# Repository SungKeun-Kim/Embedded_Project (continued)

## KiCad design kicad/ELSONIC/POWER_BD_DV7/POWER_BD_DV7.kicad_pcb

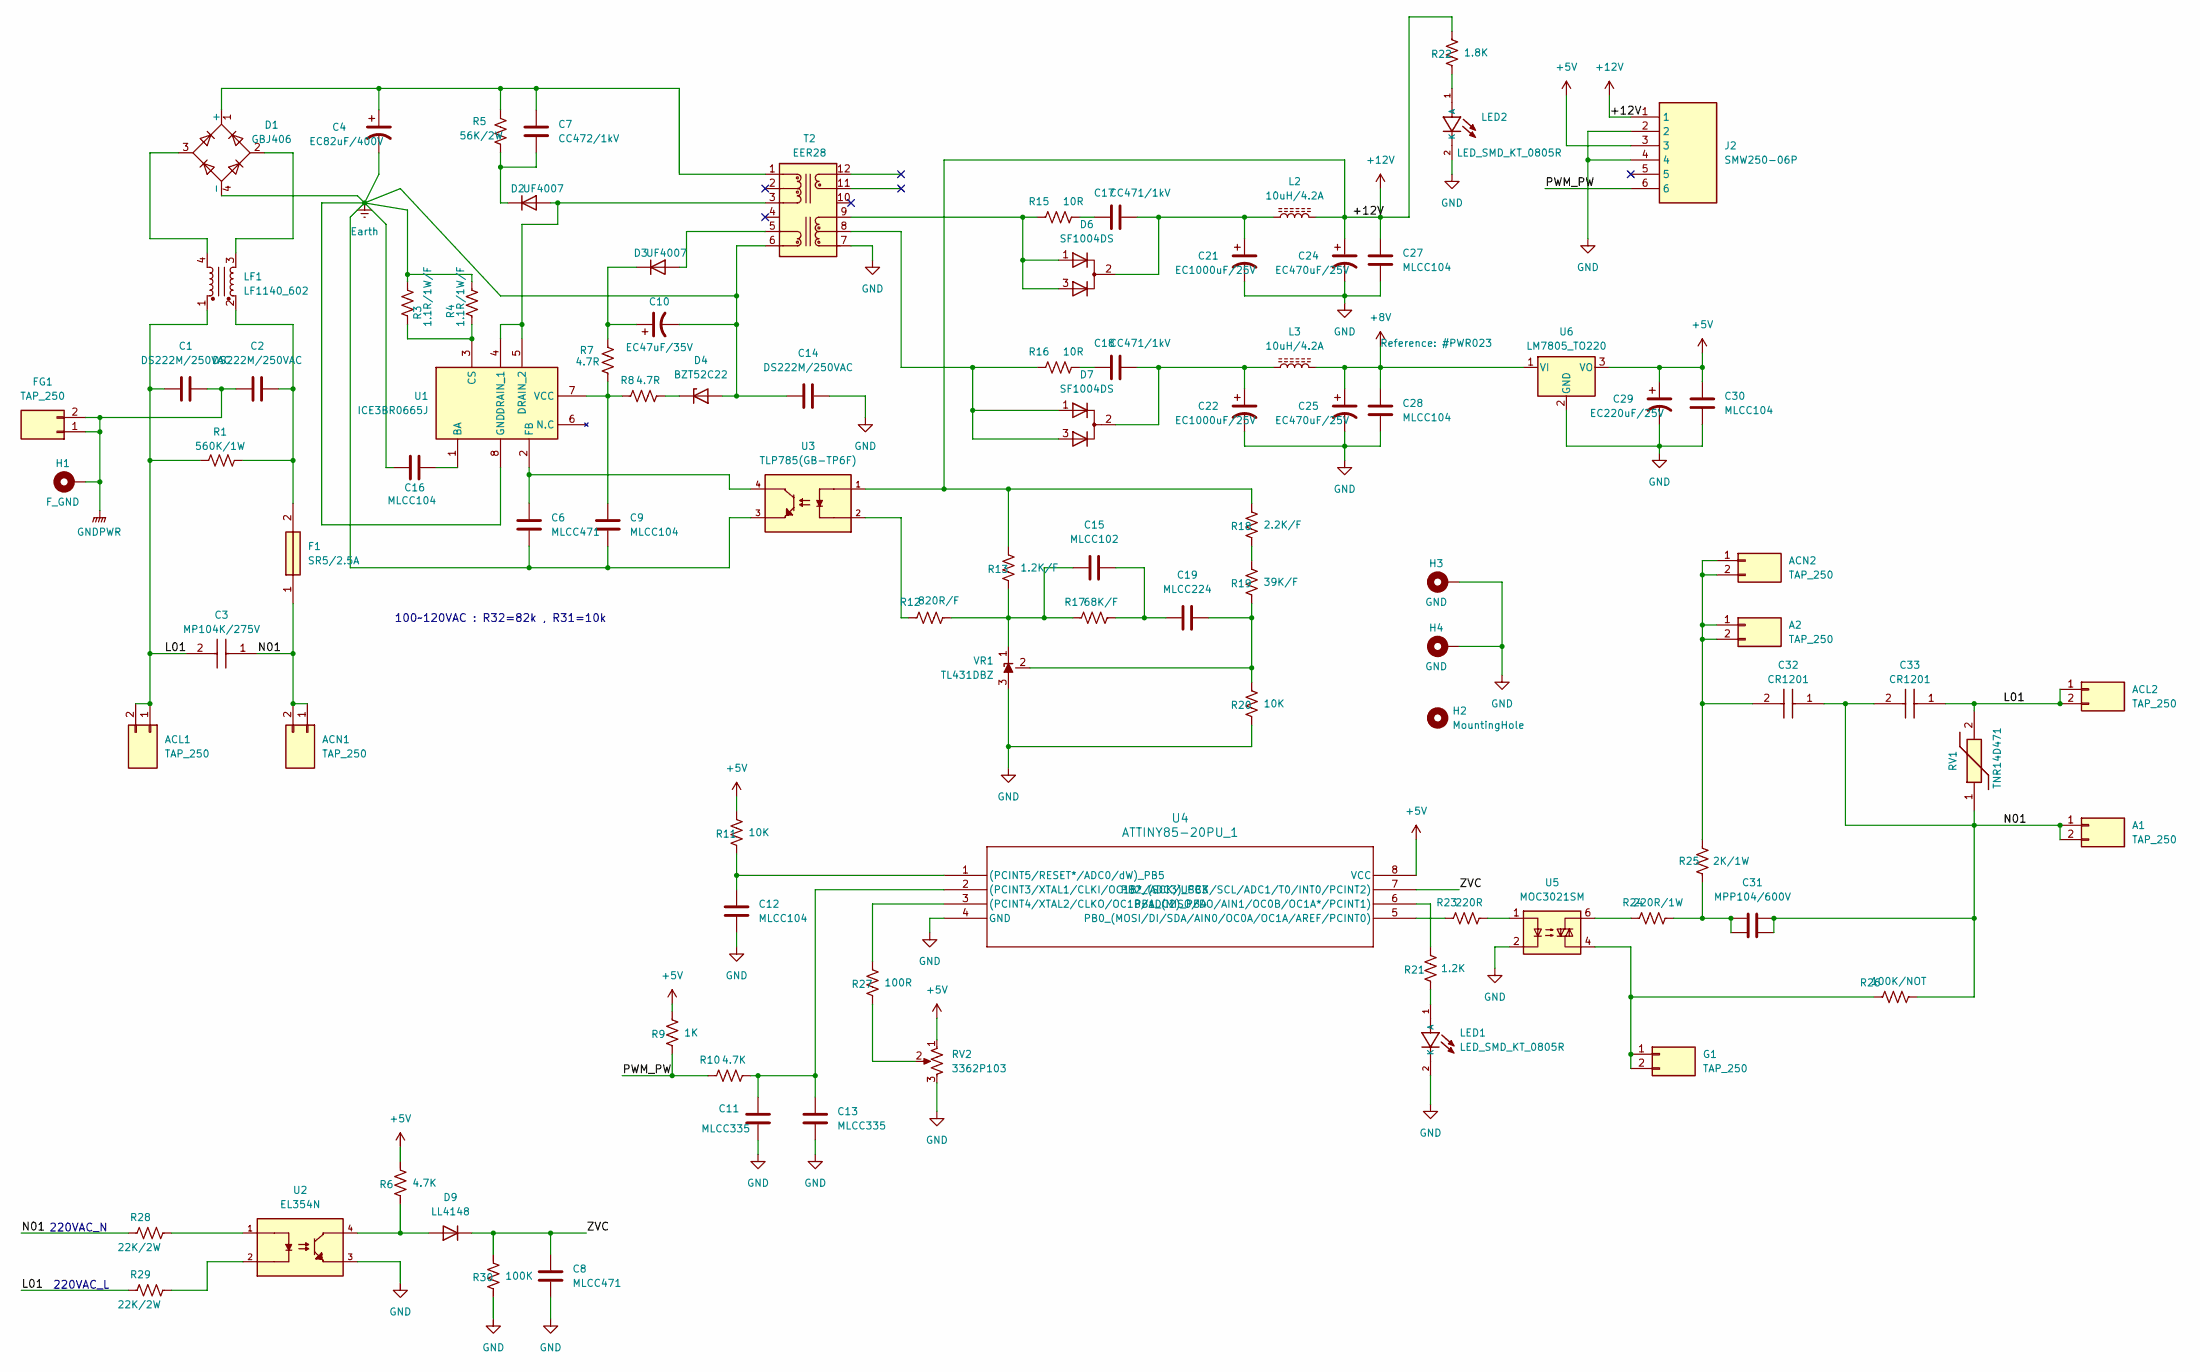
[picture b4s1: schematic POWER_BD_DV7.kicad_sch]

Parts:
A1, A2: TAP_250
ACL1, ACL2: TAP_250
ACN1, ACN2: TAP_250
C1, C2, C14: DS222M/250VAC; DS222M
C3: MP104K/275V; 104K_275V
C4: EC82uF/400V; 82uF_400V
C6, C8: MLCC471; C_3216Metric; LCSC C106069
C7: CC472/1kV; C_3216Metric; LCSC C9192
C9, C12, C16, C27, C28, C30: MLCC104; C_3216Metric; LCSC C24497
C10: EC47uF/35V; CP_Elec_6.3x5.4; LCSC C970678
C11, C13: MLCC335; C_3216Metric; LCSC C3908730
C15: MLCC102; C_3216Metric; LCSC C1941
C17, C18: CC471/1kV; C_3216Metric; LCSC C9189
C19: MLCC224; C_3216Metric; LCSC C1857
C21, C22: EC1000uF/25V; CP_Radial_D10.0mm_P5.00mm
C24, C25: EC470uF/25V; CP_Radial_D10.0mm_P5.00mm
C29: EC220uF/25V; CP_Elec_6.3x7.7; LCSC C2992606
C31: MPP104/600V; C_PP_P10.0mm_P21.2mm
C32, C33: CR1201; SPARK_KILLER
D1: GBJ406
D2, D3: UF4007; D_SMA; LCSC C81191
D4: BZT52C22; D_SOD-123; LCSC C2108
D6, D7: SF1004DS; TO-252-2; LCSC C3011035
D9: LL4148; LL4148_MELF; LCSC C68883
F1: SR5/2.5A; SR525ABK
FG1: TAP_250
G1: TAP_250
H1: F_GND; MTHole_3.5mm_7.5mmPad_GND
H2: MountingHole; MTHole_3.5mm
H3, H4: GND; MTHole_3.5mm_7.5mmPad_GND
J2: SMW250-06P; SMW250_06P
L2, L3: 10uH/4.2A; L_Sumida_CDMC6D28_7.25x6.5mm; LCSC C436542
LED1, LED2: LED_SMD_KT_0805R; LED_2012Metric; LCSC C2295
LF1: LF1140_602; LF1140
R1: 560K/1W; R_Axial_1W_P14.6mm
R3, R4: 1.1R/1W/F; R_6332Metric; LCSC C5154651
R5: 56K/2W; R_Axial_2W_P20.32mm
R6, R10: 4.7K; R_3216Metric; LCSC C17936
R7, R8: 4.7R; R_3216Metric; LCSC C2907501
R9: 1K; R_3216Metric; LCSC C4410
R11, R20: 10K; R_3216Metric; LCSC C17902
R12: 820R/F; R_3216Metric; LCSC C17984
R13: 1.2K/F; R_3216Metric; LCSC C17891
R15, R16: 10R; R_4532Metric; LCSC C2933875
R17: 68K/F; R_3216Metric; LCSC C137239
R18: 2.2K/F; R_3216Metric; LCSC C140044
R19: 39K/F; R_3216Metric; LCSC C18008
R21: 1.2K; R_3216Metric; LCSC C26035
R22: 1.8K; R_3216Metric; LCSC C102291
R23: 220R; R_3216Metric; LCSC C17957
R24: 220R/1W; R_6332Metric; LCSC C38808
R25: 2K/1W; R_6332Metric; LCSC C37457
R26: 100K/NOT; R_Axial_0.25W_P10.16mm
R27: 100R; R_3216Metric; LCSC C17901
R28, R29: 22K/2W; R_Axial_2W_P20.32mm
R30: 100K; R_3216Metric; LCSC C17900
RV1: TNR14D471; TNR14D_P7.62
RV2: 3362P103; TRIM_3362P
T2: EER28; EER28_35_12P
U1: ICE3BR0665J; DIP-8_W7.62mm_Socket
U2: EL354N; SOIC-4_EL354_P2.54mm; LCSC C188348
U3: TLP785(GB-TP6F); SOP-4_7.5x4.1mm_P2.54mm; LCSC C45445
U4: ATTINY85-20PU_1; DIP-8_W7.62mm_Socket
U5: MOC3021SM; SOIC-6_P2.54mm; LCSC C115465
U6: LM7805_TO220; TO-252-2; LCSC C21706
VR1: TL431DBZ; SOT-23-3; LCSC C23892

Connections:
+5V: C29.1, C30.2, J2.3, R6.2, R9.2, R11.2, RV2.1, U4.8 (VCC), U6.3 (VO)
+8V: C25.1, C28.2, L3.2, U6.1 (VI)
+12V: C24.1, C27.2, J2.1, L2.2, R13.2, R18.2, R22.2, U3.1
/L01: ACL1.1, ACL1.2, ACL2.1, ACL2.2, C1.1, C3.2, C33.1, LF1.1, R1.1, R29.1, RV1.2
/N01: A1.1, A1.2, ACN1.1, ACN1.2, C3.1, C31.2, C31.4, C32.1, C33.2, F1.1, R26.2, R28.1, RV1.1
/PWM_PW: J2.6, R9.1, R10.1
/ZVC: C8.2, D9.1 (K), R30.2, U4.7 (PB2_(SCK/USCK/SCL/ADC1/T0/INT0/PCINT2))
Earth: C4.2, C6.1, C9.1, C10.2, C14.1, C16.2, D1.4 (-), D4.2 (A), R3.1, R4.1, T2.6 (Vcc_GND), U1.8 (GND), U3.3
GND: C8.1, C11.1, C12.1, C13.1, C14.2, C21.2, C22.2, C24.2, C25.2, C27.1, C28.1, C29.2, C30.1, H3.1 (1_1), H4.1 (1_1), J2.2, J2.4, LED1.2 (K), LED2.2 (K), R20.1, R30.1, RV2.3, T2.7 (N_GND1), U2.3, U4.4 (GND), U5.2, U6.2 (GND), VR1.3 (A)
GNDPWR: C1.2, C2.1, FG1.1, FG1.2, H1.1 (1_1)
unnamed: A2.1, A2.2, ACN2.1, ACN2.2, C32.2, R25.1
unnamed: C2.2, F1.2, LF1.2, R1.2
unnamed: C15.2, C19.1, R17.2
unnamed: C17.1, R15.2
unnamed: C18.1, R16.2
unnamed: C31.1, C31.3, R24.2, R25.2
unnamed: C4.1, C7.1, D1.1 (+), R5.1, T2.1 (P0)
unnamed: D1.2, LF1.3
unnamed: D1.3, LF1.4
unnamed: D2.2 (A), T2.3 (P2), U1.4 (DRAIN_1), U1.5 (DRAIN_2)
unnamed: C7.2, D2.1 (K), R5.2
unnamed: D3.2 (A), T2.5 (Vcc)
unnamed: C10.1, D3.1 (K), R7.1
unnamed: D4.1 (K), R8.2
unnamed: C17.2, C21.1, D6.2 (K), L2.1
unnamed: C18.2, C22.1, D7.2 (K), L3.1
unnamed: D9.2 (A), R6.1, U2.4
unnamed: G1.1, G1.2, R26.1, U5.4
unnamed: LED1.1 (A), R21.2
unnamed: LED2.1 (A), R22.1
unnamed: R12.1, U3.2
unnamed: R18.1, R19.2
unnamed: R23.2, U5.1
unnamed: R24.1, U5.6
unnamed: R27.1, RV2.2
unnamed: R28.2, U2.1
unnamed: R29.2, U2.2
unnamed: D7.1 (A), D7.3 (A), R16.1, T2.8 (N1)
unnamed: D6.1 (A), D6.3 (A), R15.1, T2.9 (N2)
unnamed: C16.1, U1.1 (BA)
unnamed: R3.2, R4.2, U1.3 (CS)
unnamed: C6.2, U1.2 (FB), U3.4
unnamed: C9.2, R7.2, R8.1, U1.7 (VCC)
unnamed: C11.2, C13.2, R10.2, U4.2 ((PCINT3/XTAL1/CLKI/OC1B*/ADC3)_PB3)
unnamed: R27.2, U4.3 ((PCINT4/XTAL2/CLKO/OC1B/ADC2)_PB4)
unnamed: C12.2, R11.1, U4.1 ((PCINT5/RESET*/ADC0/dW)_PB5)
unnamed: R23.1, U4.5 (PB0_(MOSI/DI/SDA/AIN0/OC0A/OC1A/AREF/PC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)
unnamed: R21.1, U4.6 (PB1_(MISO/DO/AIN1/OC0B/OC1A*/PCINT1))
unnamed: C15.1, R12.2, R13.1, R17.1, VR1.1 (K)
unnamed: C19.2, R19.1, R20.2, VR1.2 (REF)

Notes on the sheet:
220VAC_N
100~120VAC : R32=82k , R31=10k
220VAC_L

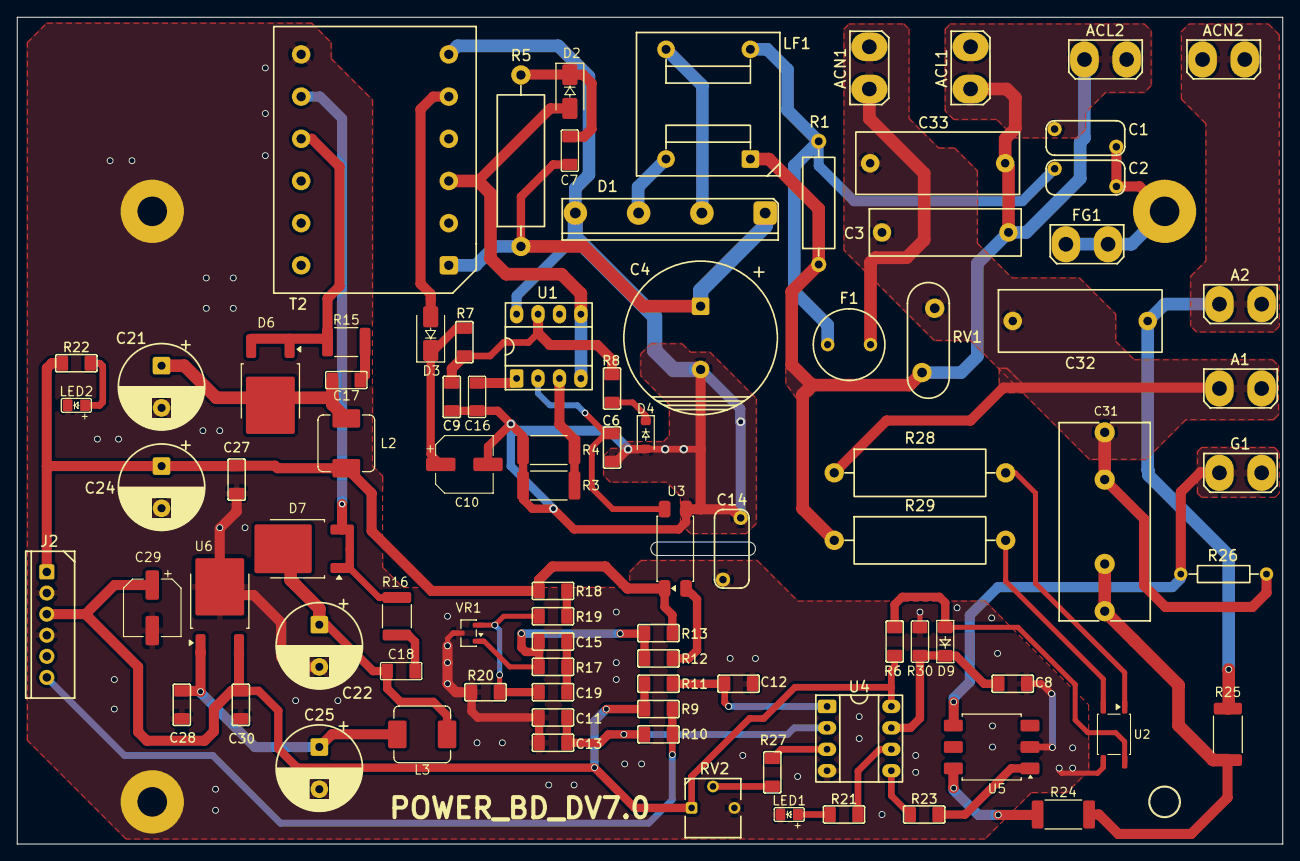
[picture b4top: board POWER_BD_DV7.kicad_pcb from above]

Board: 2 copper layers, 150.0 x 98.0 mm, 93 parts (0 on the bottom side), 50 nets.

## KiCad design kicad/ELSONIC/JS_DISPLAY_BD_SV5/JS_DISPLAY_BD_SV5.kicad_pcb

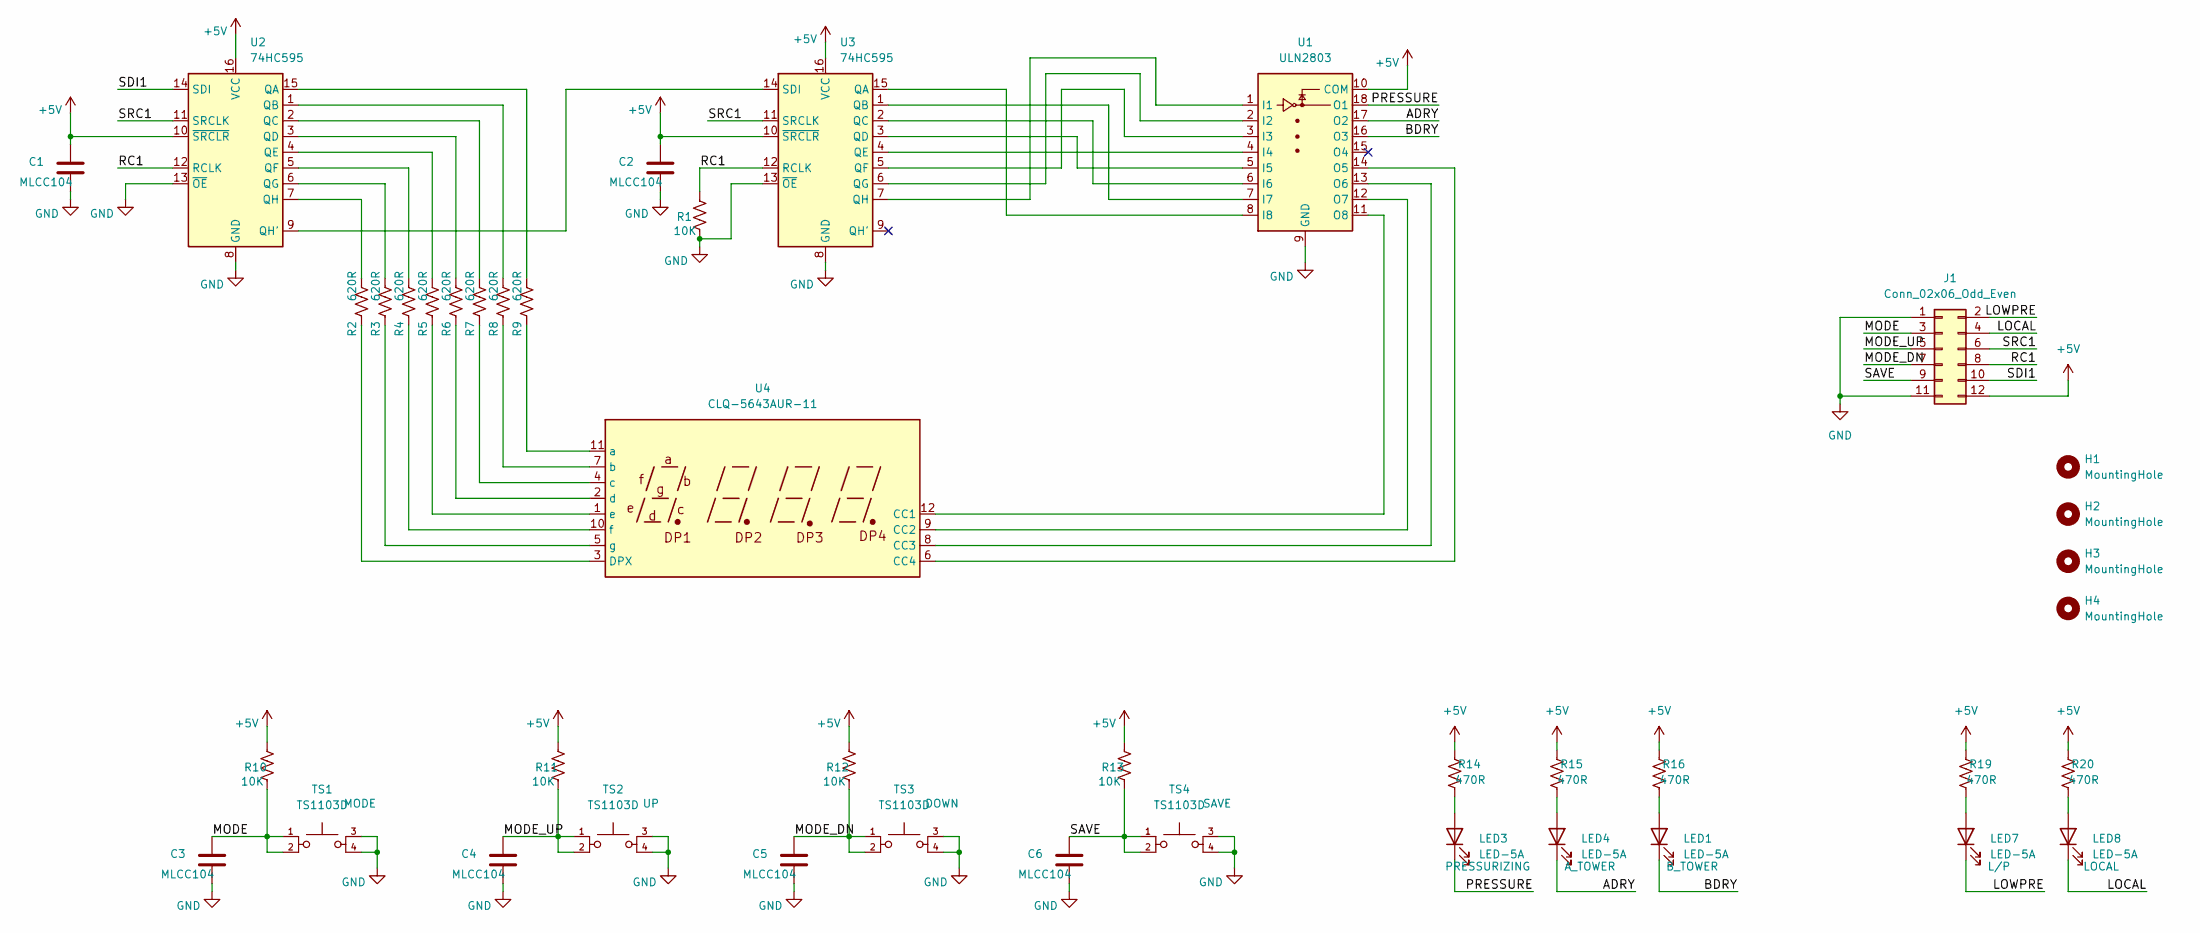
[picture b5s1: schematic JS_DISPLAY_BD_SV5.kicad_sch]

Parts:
C1, C2, C3, C4, C5, C6: MLCC104; C_3216Metric; LCSC C1945
H1, H2, H3, H4: MountingHole; MTHole_3.5mm_ANTICOPPER
J1: Conn_02x06_Odd_Even; IDC-Header_2x06_P2.54mm_Vertical
LED1, LED3, LED4, LED7, LED8: LED-5A; LED_D5.0mm
R1, R10, R11, R12, R13: 10K; R_3216Metric; LCSC C136460
R2, R3, R4, R5, R6, R7, R8, R9: 620R; R_3216Metric; LCSC C966344
R14, R15, R16, R19, R20: 470R; R_3216Metric; LCSC C114948
TS1, TS2, TS3, TS4: TS1103D; SW_PUSH-12mm
U1: ULN2803; SOP-18_7.495x11.515mm_P1.27mm; LCSC C18164409
U2, U3: 74HC595; SOIC-16_3.9x9.9mm_P1.27mm; LCSC C5947
U4: CLQ-5643AUR-11

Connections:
+5V: C1.2, C2.2, J1.12, R10.2, R11.2, R12.2, R13.2, R14.2, R15.2, R16.2, R19.2, R20.2, U1.10 (COM), U2.10 (~SRCLR), U2.16 (VCC), U3.10 (~SRCLR), U3.16 (VCC)
/ADRY: LED4.1 (K), U1.17 (O2)
/BDRY: LED1.1 (K), U1.16 (O3)
/LOCAL: J1.4, LED8.1 (K)
/LOWPRE: J1.2, LED7.1 (K)
/MODE: C3.2, J1.3, R10.1, TS1.1, TS1.2
/MODE_DN: C5.2, J1.7, R12.1, TS3.1, TS3.2
/MODE_UP: C4.2, J1.5, R11.1, TS2.1, TS2.2
/PRESSURE: LED3.1 (K), U1.18 (O1)
/RC1: J1.8, R1.2, U2.12 (RCLK), U3.12 (RCLK)
/SAVE: C6.2, J1.9, R13.1, TS4.1, TS4.2
/SDI1: J1.10, U2.14 (SDI)
/SRC1: J1.6, U2.11 (SRCLK), U3.11 (SRCLK)
GND: C1.1, C2.1, C3.1, C4.1, C5.1, C6.1, J1.1, J1.11, R1.1, TS1.3, TS1.4, TS2.3, TS2.4, TS3.3, TS3.4, TS4.3, TS4.4, U1.9 (GND), U2.8 (GND), U2.13 (~OE), U3.8 (GND), U3.13 (~OE)
unnamed: LED1.2 (A), R16.1
unnamed: LED3.2 (A), R14.1
unnamed: LED4.2 (A), R15.1
unnamed: LED7.2 (A), R19.1
unnamed: LED8.2 (A), R20.1
unnamed: U1.1 (I1), U3.7 (QH)
unnamed: U1.2 (I2), U3.6 (QG)
unnamed: U1.3 (I3), U3.5 (QF)
unnamed: U1.4 (I4), U3.4 (QE)
unnamed: U1.5 (I5), U3.3 (QD)
unnamed: U1.6 (I6), U3.2 (QC)
unnamed: U1.7 (I7), U3.1 (QB)
unnamed: U1.8 (I8), U3.15 (QA)
unnamed: U1.14 (O5), U4.6 (CC4)
unnamed: U1.13 (O6), U4.8 (CC3)
unnamed: U1.12 (O7), U4.9 (CC2)
unnamed: U1.11 (O8), U4.12 (CC1)
unnamed: R9.2, U2.15 (QA)
unnamed: R8.2, U2.1 (QB)
unnamed: R7.2, U2.2 (QC)
unnamed: R6.2, U2.3 (QD)
unnamed: R5.2, U2.4 (QE)
unnamed: R4.2, U2.5 (QF)
unnamed: R3.2, U2.6 (QG)
unnamed: U2.9 (QH'), U3.14 (SDI)
unnamed: R2.2, U2.7 (QH)
unnamed: R2.1, U4.3 (DPX)
unnamed: R9.1, U4.11 (a)
unnamed: R8.1, U4.7 (b)
unnamed: R7.1, U4.4 (c)
unnamed: R6.1, U4.2 (d)
unnamed: R5.1, U4.1 (e)
unnamed: R4.1, U4.10 (f)
unnamed: R3.1, U4.5 (g)

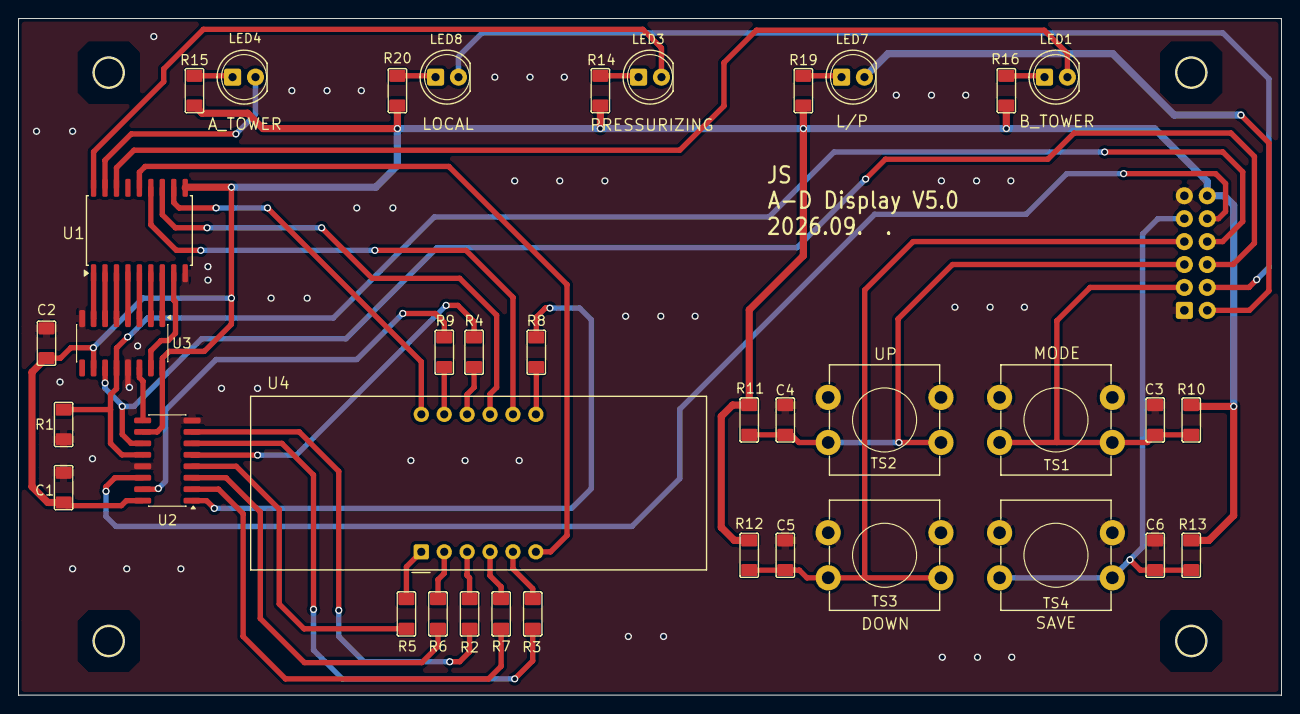
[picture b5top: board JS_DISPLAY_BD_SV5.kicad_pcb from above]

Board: 2 copper layers, 140.0 x 75.0 mm, 42 parts (1 on the bottom side), 48 nets.

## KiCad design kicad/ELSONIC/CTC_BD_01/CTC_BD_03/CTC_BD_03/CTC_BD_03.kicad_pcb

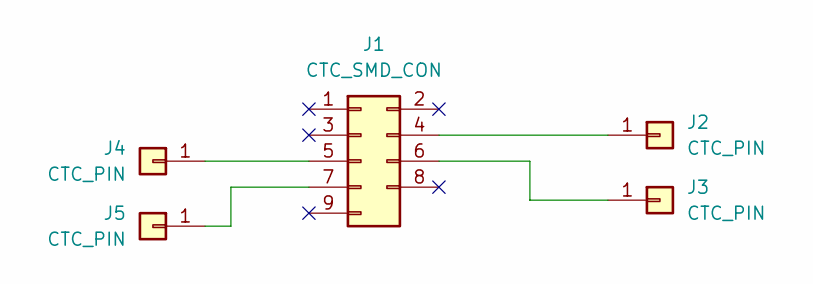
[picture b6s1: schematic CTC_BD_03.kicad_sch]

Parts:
J1: CTC_SMD_CON
J2, J3, J4, J5: CTC_PIN

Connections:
unnamed: J1.4, J2.1 (Pin_1_1)
unnamed: J1.5, J4.1 (Pin_1_1)
unnamed: J1.6, J3.1 (Pin_1_1)
unnamed: J1.7, J5.1 (Pin_1_1)

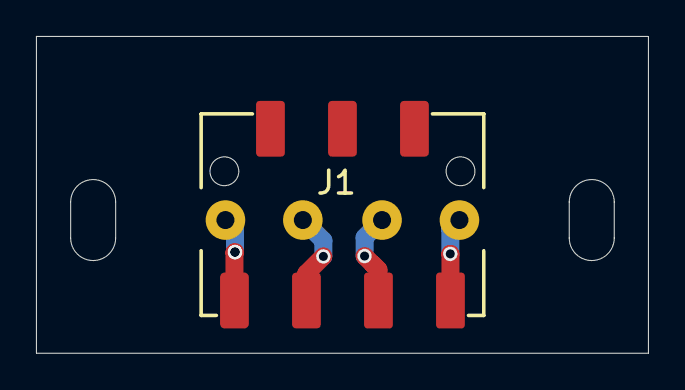
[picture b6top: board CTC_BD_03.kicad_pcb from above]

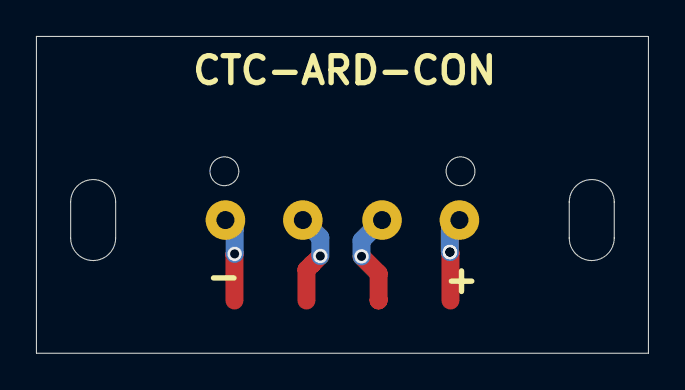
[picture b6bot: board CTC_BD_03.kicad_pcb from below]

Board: 2 copper layers, 34.0 x 17.6 mm, 5 parts (4 on the bottom side), 4 nets.

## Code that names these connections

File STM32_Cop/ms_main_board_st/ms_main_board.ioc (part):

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Mcu.Name=STM32G474R(B-C-E)Tx
Mcu.Package=LQFP64
Mcu.UserName=STM32G474RBTx
PA0.GPIOParameters=GPIO_Label
PA0.GPIO_Label=ADC1_IN1
PA0.Signal=ADC1_IN1
PA1.GPIOParameters=GPIO_Label
PA1.GPIO_Label=ADC1_IN2
PA1.Signal=ADC1_IN2
PA10.GPIOParameters=GPIO_Label
PA10.GPIO_Label=LOW_ALARM
PA10.Signal=GPIO_Output
PA11.GPIOParameters=GPIO_Label
PA11.GPIO_Label=GOING
PA11.Signal=GPIO_Output
PA12.GPIOParameters=GPIO_Label
PA12.GPIO_Label=TOTAL_ALARM
PA12.Signal=GPIO_Output
PA13.GPIOParameters=GPIO_Label
PA13.GPIO_Label=SWDIO
PA13.Mode=Serial_Wire
PA13.Signal=SYS_JTMS-SWDIO
PA14.GPIOParameters=GPIO_Label
PA14.GPIO_Label=SWCLK
PA14.Mode=Serial_Wire
PA14.Signal=SYS_JTCK-SWCLK
PA15.GPIOParameters=GPIO_PuPd,GPIO_Label
PA15.GPIO_Label=REMOTE_M
PA15.GPIO_PuPd=GPIO_PULLUP
PA15.Signal=GPIO_Input
PA2.GPIOParameters=GPIO_Speed,GPIO_Label
PA2.GPIO_Label=USART2_TX
PA2.GPIO_Speed=GPIO_SPEED_FREQ_HIGH
PA2.Signal=USART2_TX
PA3.GPIOParameters=GPIO_Speed,GPIO_PuPd,GPIO_Label
PA3.GPIO_Label=USART2_RX
PA3.GPIO_PuPd=GPIO_PULLUP
PA3.GPIO_Speed=GPIO_SPEED_FREQ_HIGH
PA3.Signal=USART2_RX
PA4.GPIOParameters=GPIO_Label
PA4.GPIO_Label=DAC1_OUT1
PA4.Signal=COMP_DAC11_group
PA6.GPIOParameters=GPIO_Label
PA6.GPIO_Label=ADC2_IN3
PA6.Signal=ADC2_IN3
PA7.GPIOParameters=GPIO_Label
PA7.GPIO_Label=ADC2_IN4
PA7.Signal=ADC2_IN4
PA8.GPIOParameters=GPIO_Speed,GPIO_Label
PA8.GPIO_Label=CHA1
PA8.GPIO_Speed=GPIO_SPEED_FREQ_VERY_HIGH
PA8.Signal=HRTIM1_CHA1
PA9.GPIOParameters=GPIO_Speed,GPIO_Label
PA9.GPIO_Label=CHA2
PA9.GPIO_Speed=GPIO_SPEED_FREQ_VERY_HIGH
PA9.Signal=HRTIM1_CHA2
PB0.GPIOParameters=GPIO_Speed,GPIO_Label
PB0.GPIO_Label=DE_RS485
PB0.GPIO_Speed=GPIO_SPEED_FREQ_HIGH
PB0.Signal=GPIO_Output
PB1.GPIOParameters=GPIO_Speed,GPIO_Label
PB1.GPIO_Label=RE_RS485_N
PB1.GPIO_Speed=GPIO_SPEED_FREQ_HIGH
PB1.Signal=GPIO_Output
PB10.GPIOParameters=GPIO_Speed,GPIO_Label
PB10.GPIO_Label=D0
PB10.GPIO_Speed=GPIO_SPEED_FREQ_MEDIUM
PB10.Signal=GPIO_Output
PB11.GPIOParameters=GPIO_Speed,GPIO_Label
PB11.GPIO_Label=D1
PB11.GPIO_Speed=GPIO_SPEED_FREQ_MEDIUM
PB11.Signal=GPIO_Output
PB12.GPIOParameters=GPIO_Speed,GPIO_Label
PB12.GPIO_Label=D2
PB12.GPIO_Speed=GPIO_SPEED_FREQ_MEDIUM
PB12.Signal=GPIO_Output
PB13.GPIOParameters=GPIO_Speed,GPIO_Label
PB13.GPIO_Label=D3
PB13.GPIO_Speed=GPIO_SPEED_FREQ_MEDIUM
PB13.Signal=GPIO_Output
PB14.GPIOParameters=GPIO_Speed,GPIO_Label
PB14.GPIO_Label=D4
PB14.GPIO_Speed=GPIO_SPEED_FREQ_MEDIUM
PB14.Signal=GPIO_Output
PB15.GPIOParameters=GPIO_Speed,GPIO_Label
PB15.GPIO_Label=D5
PB15.GPIO_Speed=GPIO_SPEED_FREQ_MEDIUM
PB15.Signal=GPIO_Output
PB3.GPIOParameters=GPIO_Label
PB3.GPIO_Label=HIGH_ALARM
PB3.Signal=GPIO_Output
PB4.GPIOParameters=GPIO_Label
PB4.GPIO_Label=TD_ALARM
PB4.Signal=GPIO_Output
PB6.GPIOParameters=GPIO_Speed,GPIO_Label
PB6.GPIO_Label=USART1_TX
PB6.GPIO_Speed=GPIO_SPEED_FREQ_HIGH
PB6.Signal=USART1_TX
PB7.GPIOParameters=GPIO_Speed,GPIO_Label
PB7.GPIO_Label=USART1_RX
PB7.GPIO_Speed=GPIO_SPEED_FREQ_HIGH
PB7.Signal=USART1_RX
PB8-BOOT0.GPIOParameters=GPIO_PuPd,GPIO_Label
PB8-BOOT0.GPIO_Label=BOOT0
PB8-BOOT0.GPIO_PuPd=GPIO_NOPULL
PB8-BOOT0.Signal=GPIO_Input
PC0.GPIOParameters=GPIO_PuPd,GPIO_Label
PC0.GPIO_Label=START_STOP
PC0.GPIO_PuPd=GPIO_PULLUP
PC0.Signal=GPIO_Input
PC1.GPIOParameters=GPIO_PuPd,GPIO_Label
PC1.GPIO_Label=MODE
PC1.GPIO_PuPd=GPIO_PULLUP
PC1.Signal=GPIO_Input
PC10.GPIOParameters=GPIO_PuPd,GPIO_Label
PC10.GPIO_Label=BCD_BIT1
PC10.GPIO_PuPd=GPIO_PULLUP
PC10.Signal=GPIO_Input
PC11.GPIOParameters=GPIO_PuPd,GPIO_Label
PC11.GPIO_Label=BCD_BIT2
PC11.GPIO_PuPd=GPIO_PULLUP
PC11.Signal=GPIO_Input
PC12.GPIOParameters=GPIO_PuPd,GPIO_Label
PC12.GPIO_Label=BCD_BIT3
PC12.GPIO_PuPd=GPIO_PULLUP
PC12.Signal=GPIO_Input
PC14-OSC32_IN.GPIOParameters=GPIO_Speed,GPIO_Label
PC14-OSC32_IN.GPIO_Label=CLK_LCD
PC14-OSC32_IN.GPIO_Speed=GPIO_SPEED_FREQ_MEDIUM
PC14-OSC32_IN.Signal=GPIO_Output
PC15-OSC32_OUT.GPIOParameters=GPIO_Speed,GPIO_Label
PC15-OSC32_OUT.GPIO_Label=CLK_LED
PC15-OSC32_OUT.GPIO_Speed=GPIO_SPEED_FREQ_MEDIUM
PC15-OSC32_OUT.Signal=GPIO_Output
PC2.GPIOParameters=GPIO_PuPd,GPIO_Label
PC2.GPIO_Label=UP
PC2.GPIO_PuPd=GPIO_PULLUP
PC2.Signal=GPIO_Input
PC3.GPIOParameters=GPIO_PuPd,GPIO_Label
PC3.GPIO_Label=DOWN
PC3.GPIO_PuPd=GPIO_PULLUP
PC3.Signal=GPIO_Input
PC4.GPIOParameters=GPIO_PuPd,GPIO_Label
PC4.GPIO_Label=SET
PC4.GPIO_PuPd=GPIO_PULLUP
PC4.Signal=GPIO_Input
PC5.GPIOParameters=GPIO_Label
PC5.GPIO_Label=BZ_OUT
PC5.Signal=GPIO_Output
PC6.GPIOParameters=GPIO_Label
PC6.GPIO_Label=LC_REL1
PC6.Signal=GPIO_Output
PC7.GPIOParameters=GPIO_Label
PC7.GPIO_Label=LC_REL2
PC7.Signal=GPIO_Output
PC8.GPIOParameters=GPIO_Label
PC8.GPIO_Label=LC_REL3
PC8.Signal=GPIO_Output
PC9.GPIOParameters=GPIO_Label
PC9.GPIO_Label=LC_REL4
PC9.Signal=GPIO_Output
PD2.GPIOParameters=GPIO_PuPd,GPIO_Label
PD2.GPIO_Label=SENSOR
PD2.GPIO_PuPd=GPIO_PULLUP
PD2.Signal=GPIO_Input
PF0-OSC_IN.Signal=RCC_OSC_IN
PF1-OSC_OUT.Signal=RCC_OSC_OUT
RCC.HSEState=RCC_HSE_ON
RCC.HSE_VALUE=8000000
RCC.SYSCLKFreq_VALUE=170000000
RCC.SYSCLKSource=RCC_SYSCLKSOURCE_PLLCLK
RCC.SYSCLKSourceVirtual=RCC_SYSCLKSOURCE_PLLCLK
board=custom

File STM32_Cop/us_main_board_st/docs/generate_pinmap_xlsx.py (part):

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
    groups = [
        ("🔊 초음파 발진 (TIM1 고급 타이머)", FILL_PWM, [
            ["PA8",  35, "TIM1_CH1 (AF6)",  "초음파 PWM 출력 — 하이사이드 게이트 드라이버(HIN) 입력", "Output", "Very High"],
            ["PB13", 28, "TIM1_CH1N (AF6)", "초음파 PWM 상보 출력 — 로우사이드 게이트 드라이버(LIN) 입력", "Output", "Very High"],
        ]),
        ("⚡ 위상제어 조광기 출력 (TIM3 → ATtiny85)", FILL_PWM, [
            ["PB0", 22, "TIM3_CH3 (AF2)", "ATtiny85 위상제어 듀티 지령 전달용 3kHz PWM 출력", "Output", "Medium"],
        ]),
        ("📡 내장 아날로그 — 비교기(COMP) + DAC3 + TIM2 캡처", FILL_INTERNAL, [
            ["PA1",  13, "COMP1_INP",              "전압(V) 위상 제로크로싱 검출 — 비교기 양(+)입력 【전용, ADC 비공유】", "Analog", "—"],
            ["PA7",  19, "COMP2_INP",              "전류(I) 위상 제로크로싱 검출 — 비교기 양(+)입력 (CT센서) 【전용, GPIO 비공유】", "Analog", "—"],
            ["—",    "—", "DAC3_CH1 → COMP1_INM",  "COMP1 반전입력 기준전압 (~1.65V = VDDA/2) 【내부 크로스바, 외부핀 없음】", "Internal", "—"],
            ["—",    "—", "DAC3_CH2 → COMP2_INM",  "COMP2 반전입력 기준전압 (~1.65V = VDDA/2) 【내부 크로스바, 외부핀 없음】", "Internal", "—"],
            ["—",    "—", "COMP1_OUT → TIM2_IC1",  "전압 제로크로싱 타임스탬프 캡처 【내부 라우팅】", "Internal", "—"],
            ["—",    "—", "COMP2_OUT → TIM2_IC2",  "전류 제로크로싱 타임스탬프 캡처 【내부 라우팅】", "Internal", "—"],
        ]),
        ("🎛️ ADC 입력 (가변저항 + 전류 센서)", FILL_ANALOG, [
            ["PA0",  12, "ADC1_IN1",  "보드 내장 가변저항 전압 (초음파 출력/위상 레벨)", "Analog", "—"],
            ["PB11", 26, "ADC1_IN14", "외부 판넬 가변저항 전압 (외부 출력/위상 레벨 지정)", "Analog", "—"],
            ["PA4",  16, "ADC2_IN17", "AC 전원 입력단 시스템 소모 전류 측정용 (ACS722/TMCS1100)", "Analog", "—"],
        ]),
        ("📺 LCD1602 (4비트 병렬 모드)", FILL_LCD, [
            ["PB12", 27, "GPIO_Output", "LCD RS (Register Select)", "Output", "Low"],
            ["PB14", 29, "GPIO_Output", "LCD EN (Enable)", "Output", "Low"],
            ["PB15", 30, "GPIO_Output", "LCD D4", "Output", "Low"],
            ["PC6",  31, "GPIO_Output", "LCD D5", "Output", "Low"],
            ["PC7",  32, "GPIO_Output", "LCD D6", "Output", "Low"],
            ["PC8",  33, "GPIO_Output", "LCD D7", "Output", "Low"],
        ]),
        ("🔘 택트 스위치 (내부 풀업, Active LOW)", FILL_BTN, [
            ["PC0", 8,  "GPIO_Input (PU)", "BTN_MENU — 메뉴 진입 및 상위 메뉴 복귀", "Input", "—"],
            ["PC1", 9,  "GPIO_Input (PU)", "BTN_UP — 메뉴 위로 / 값 증가", "Input", "—"],
            ["PC2", 10, "GPIO_Input (PU)", "BTN_DOWN — 메뉴 아래로 / 값 감소", "Input", "—"],
            ["PC3", 11, "GPIO_Input (PU)", "BTN_OK — 선택/확인 및 초음파 Start/Stop 겸용", "Input", "—"],
        ]),
        ("🔌 Modbus RS485 (USART2 + 방향 제어)", FILL_COMM, [
            ["PA2",  14, "USART2_TX (AF7)",    "RS485 TXD", "AF Output", "Very High"],
            ["PA3",  15, "USART2_RX (AF7)",    "RS485 RXD", "AF Input", "—"],
            ["PA5",  17, "GPIO_Output",         "RS485 DE (Driver Enable, HIGH=송신) — USART2 인접 배치", "Output", "High"],
            ["PA6",  18, "GPIO_Output",         "RS485 /RE (Receiver Enable, LOW=수신) — USART2 인접 배치", "Output", "High"],
            ["PC11", 46, "GPIO_Output",         "RS485 RTERM (종단 저항 120Ω ON/OFF 제어)", "Output", "Low"],
            ["PC12", 47, "GPIO_Input",          "Board_Detect (RS485 옵션 보드 장착 인식, 메뉴 연동)", "Input", "—"],
        ]),
        ("🔧 외부 제어 인터페이스 (스위치 입력 + 릴레이/부저 출력)", FILL_EXT, [
            ["PC4",  20, "GPIO_Output", "부저 출력 — 버튼 클릭음 + 에러 알람 겸용", "Output", "Low"],
            ["PC5",  21, "GPIO_Output", "End Signal 릴레이 — 사이클 종료 후 0.5초 ON", "Output", "Low"],
            ["PA12", 39, "GPIO_Output", "Fault 릴레이 — 에러 발생 상태 지시", "Output", "Low"],
            ["PA15", 44, "GPIO_Output", "Running 릴레이 — 정상 동작 상태 지시 (G4는 SWD 기본, 바로 사용)", "Output", "Low"],
            ["PB1",  23, "GPIO_Input",  "Remote ON/OFF — 외부 기기 리모트 제어 입력", "Input", "—"],
            ["PB2",  24, "GPIO_Input",  "Sweep 스위치 — 수동 스윕 분산 기능 푸쉬락", "Input", "—"],
            ["PB10", 25, "GPIO_Input",  "Timer 스위치 — 내장 타이머 사용 유무 푸쉬락", "Input", "—"],
        ]),
        ("🐛 디버그 / 시스템", FILL_DBG, [
            ["PA9",  36, "USART1_TX (AF7)", "디버그 메시지용 UART TX (115200bps, 선택사항)", "AF Output", "High"],
            ["PA10", 37, "USART1_RX (AF7)", "디버그 메시지 수신용 UART RX (선택사항)", "AF Input", "—"],
            ["PA13", 40, "SWDIO",           "SWD 데이터 입출력 — GPIO 사용 금지 ⛔", "SWD", "—"],
            ["PA14", 43, "SWCLK",           "SWD 클럭 입력 — GPIO 사용 금지 ⛔", "SWD", "—"],
            ["PB3",  49, "SWO",             "Serial Wire Output — Trace용 (선택사항, 보통 생략)", "SWD", "—"],
            ["PC10", 45, "GPIO_Output",     "상태 LED — Run/Error 토글 표시", "Output", "Low"],
            ["NRST",  7, "RESET",           "MCU 리셋 (ST-Link 연결 강력 권장)", "System", "—"],
            ["BOOT0",54, "—",               "부트 모드 선택 (HIGH=부트로더, 점퍼/버튼 권장)", "System", "—"],
        ]),
        ("📦 I2C 확장 (EEPROM 등, 선택사항)", FILL_COMM, [
            ["PB8", 55, "I2C1_SCL (AF4)", "I2C EEPROM SCL (파라미터 저장 확장용)", "AF OD", "High"],
            ["PB9", 56, "I2C1_SDA (AF4)", "I2C EEPROM SDA (파라미터 저장 확장용)", "AF OD", "High"],
        ]),
        ("🔓 여유(Spare) 핀", FILL_SPARE, [
            ["PC9",  34, "—", "GPIO 자유 사용 (RS485 DE 이전 핀)", "—", "—"],
            ["PA11", 38, "—", "TIM1_CH4(AF11) 또는 GPIO", "—", "—"],
            ["PB4",  50, "—", "GPIO 또는 TIM16_CH1(AF1)", "—", "—"],
            ["PB5",  51, "—", "GPIO 또는 SPI1_MOSI(AF5)", "—", "—"],
            ["PB6",  52, "—", "I2C1_SCL(AF4) 확장 또는 GPIO", "—", "—"],
            ["PB7",  53, "—", "I2C1_SDA(AF4) 확장 또는 GPIO", "—", "—"],
            ["PD2",  48, "—", "TIM3_ETR(AF2) 또는 GPIO", "—", "—"],
        ]),
    ]

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        ["DAC3", "CH1", "→ COMP1_INM (내부)", "없음 (내부 전용)", "✅ 사용", "기준전압 공급"],
        ["DAC3", "CH2", "→ COMP2_INM (내부)", "없음 (내부 전용)", "✅ 사용", "기준전압 공급"],
        ["DAC4", "CH1/CH2", "내부 전용 (예비)", "없음", "🔵 예비", "COMP5~7 확장용"],
        ["DAC1", "CH1", "PA4", "ADC2_IN17 (전류센서)", "🔴 충돌", "사용 불가"],
        ["DAC1", "CH2", "PA5", "RS485 DE", "🔴 충돌", "사용 불가"],
        ["DAC2", "CH1", "PA6", "RS485 /RE", "🔴 충돌", "사용 불가"],
    ]
    for rd in dac_data:
        fill = FILL_OK if "✅" in str(rd[4]) else (FILL_WARN if "🔴" in str(rd[4]) else FILL_WHITE)
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    write_header_row(ws, r, oa_headers)
    r += 1
    oa_data = [
        ["OPAMP1", "PA1, PA3, PA7", "PA2", "COMP1, USART2_RX/TX", "🔴 사용불가", ""],
        ["OPAMP2", "PA7", "PA6", "COMP2, RS485 /RE", "🔴 사용불가", ""],
        ["OPAMP3", "PB0, PB13, PA1", "PB1", "TIM3_CH3, TIM1_CH1N, Remote", "🔴 사용불가", ""],
        ["OPAMP4", "PB13, PB11", "PB12", "TIM1_CH1N, 외부VR, LCD RS", "🔴 사용불가", ""],
        ["OPAMP5", "PB14, PC3", "PA8", "LCD EN, BTN_OK, TIM1_CH1", "🔴 사용불가", ""],
        ["OPAMP6", "PB12", "PB11", "LCD RS, 외부VR ADC", "🔴 사용불가", ""],
    ]
    for rd in oa_data:
        write_data_row(ws, r, rd, font=FONT_WARN, fill=FILL_WARN)
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        ("◀ Left Side (Pin 1 ~ 16)", [
            [1,  "VBAT", "—",           "Power",          "배터리 백업 (미사용 시 VDD 연결)", "전원", FILL_PWR],
            [2,  "PC13", "—",           "—",              "(미사용)", "—", FILL_PWR],
            [3,  "PC14", "—",           "—",              "(미사용, OSC32_IN)", "—", FILL_PWR],
            [4,  "PC15", "—",           "—",              "(미사용, OSC32_OUT)", "—", FILL_PWR],
            [5,  "PH0",  "—",           "—",              "OSC_IN (HSE 사용 시) 또는 미사용", "클럭", FILL_PWR],
            [6,  "PH1",  "—",           "—",              "OSC_OUT (HSE 사용 시) 또는 미사용", "클럭", FILL_PWR],
            [7,  "NRST", "—",           "RESET",          "MCU 리셋 (ST-Link 연결 강력 권장)", "디버그", FILL_DBG],
            [8,  "PC0",  "—",           "GPIO_Input (PU)","BTN_MENU — 메뉴 진입/복귀", "택트 스위치", FILL_BTN],
            [9,  "PC1",  "—",           "GPIO_Input (PU)","BTN_UP — 위로/값 증가", "택트 스위치", FILL_BTN],
            [10, "PC2",  "—",           "GPIO_Input (PU)","BTN_DOWN — 아래로/값 감소", "택트 스위치", FILL_BTN],
            [11, "PC3",  "—",           "GPIO_Input (PU)","BTN_OK — 선택/확인, Start/Stop", "택트 스위치", FILL_BTN],
            [12, "PA0",  "ADC1_IN1",    "ADC Analog",     "보드 내장 가변저항 (출력/위상 레벨)", "ADC", FILL_ANALOG],
            [13, "PA1",  "COMP1_INP",   "Analog",         "전압(V) 위상 제로크로싱 검출 비교기 (+)", "COMP", FILL_INTERNAL],
            [14, "PA2",  "USART2_TX",   "AF7",            "RS485 TXD", "RS485", FILL_COMM],
            [15, "PA3",  "USART2_RX",   "AF7",            "RS485 RXD", "RS485", FILL_COMM],
            [16, "PA4",  "ADC2_IN17",   "ADC Analog",     "AC 전류 센서 (ACS722/TMCS1100)", "ADC", FILL_ANALOG],
        ]),
        ("▼ Bottom Side (Pin 17 ~ 32)", [
            [17, "PA5",  "—",            "GPIO_Output",   "RS485 DE (HIGH=송신) — USART2 인접", "RS485", FILL_COMM],
            [18, "PA6",  "—",            "GPIO_Output",   "RS485 /RE (LOW=수신) — USART2 인접", "RS485", FILL_COMM],
            [19, "PA7",  "COMP2_INP",    "Analog",        "전류(I) 위상 제로크로싱 비교기 (+) CT센서", "COMP", FILL_INTERNAL],
            [20, "PC4",  "—",            "GPIO_Output",   "부저 (조작음 + 에러 알람 겸용)", "외부 제어", FILL_EXT],
            [21, "PC5",  "—",            "GPIO_Output",   "End Signal 릴레이 (사이클 종료 0.5s)", "외부 제어", FILL_EXT],
            [22, "PB0",  "TIM3_CH3",     "AF2",           "ATtiny85 3kHz PWM (위상제어 지령)", "위상제어", FILL_PWM],
            [23, "PB1",  "—",            "GPIO_Input",    "Remote ON/OFF (외부 리모트 제어)", "외부 제어", FILL_EXT],
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
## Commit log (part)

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2025-12-04 Initial commit: Setup project structure
2025-12-04 Add: ATtiny85 AC dimmer project with phase control
2025-12-04 Add KiCad library files and reorganize folder structure
2025-12-12 Add STM32 PWM_CDS_CLCD_TEST_01 to gitignore
2025-12-17 Initial commit with all embedded projects
2025-12-18 ATtiny85 AC Dimmer 최종 최적화 (50μs 주기, 159단계 분해능, 100%~5% 조광, 문서화 완료)
2025-12-18 main.cpp 주석 오류 수정 (100μs 50μs)
2025-12-26 Fix AC dimmer code: improve debouncing, extend timing range, standardize types, add main() function
    - Changed variable types from 'boolean' to 'bool'
    - Added time-based debouncing (2ms) for zero-cross detection
    - Adjusted MAX_DIM from 158 to maintain 5% minimum brightness
    - Fixed include order (Arduino.h first)
    - Added main() function for ATtiny framework compatibility
    - Disabled LTO in platformio.ini for proper linking
2025-12-26 Update KiCAD libraries: Add TL431 components and passive footprints
2025-12-27 dimValue 초기화 및 ISR 최적화 - dimValue를 MAX_DIM으로 초기화 (안정성 향상) - digitalWrite를 직접 PORTB 레지스터로 변경 (ISR 최적화) - dimValue 업데이트 시 cli/sei로 원자성 보장 - 미사용 zeroCrossDetect() 프로토타입 삭제
2026-01-04 Update KiCAD schematic and library files
2026-02-06 Attiny85-Dimmer: ADC 보정 수정 및 main.cpp 업데이트
2026-02-06 KiCAD MyLib: 심볼/풋프린트 라이브러리 업데이트 및 정리
2026-02-06 POWER_BD_NV2: PCB/회로도 업데이트 및 거버 파일 추가
2026-02-06 MAIN_BD_NV1: 신규 프로젝트 추가
2026-02-06 POWER_BD_SV2: 신규 프로젝트 추가
2026-02-18 자동보정 구현: minDim/maxDim 기준 - setup()에서 ZC 주기 측정 후 minDim/maxDim 동적 계산 - maxDim = avgPeriod - 6 (margin) - minDim = avgPeriod * 62 / 166 - 2 - 50Hz/60Hz 및 오실레이터 편차 자동 대응
2026-02-18 프로젝트 전체 정리: KiCAD 파일 업데이트, 불필요한 파일 삭제
2026-02-18 빠른칩 버전: minDim offset -4
2026-02-18 느린칩 버전: maxDim margin 6 (MAX_DIM_MARGIN=6)
2026-02-18 느린칩 버전: minDim offset -5, maxDim margin 6
2026-02-18 ZC 측정 개선 (상승엣지 정밀측정) + minDim offset -4
2026-02-19 느린칩 버전: maxDim margin 7 (MAX_DIM_MARGIN=7)
2026-02-19 Timer1 기반 캘리브레이션 + 기준값 설정 (margin=9, offset=-1)
2026-02-20 bestO.K
2026-02-25 JLCPCB에 POWER_BD주문
2026-02-25 폴더이름변경 AVR-->AVR_Cop
2026-02-25 파일정리 및 copilot과 cursor 분리
2026-02-25 파일정리
2026-02-25 Timer1 interrupt configuration updated to activate only the compare match A interrupt for a 50μs period.
2026-02-27 02/28
2026-03-01 26/03/01 파일정리
2026-03-02 dimmer 최종수정
    Made-with: Cursor
2026-03-10 Updated dimmer settings and final adjustments made.
2026-03-11 attiny85 2sec delay-260312
2026-03-11 2sec_Delay 260312
2026-03-11 Copilot 규칙 만듬_260312
2026-03-23 메가소닉 지침서 완료 2603
2026-03-23 Ultrasonic Gen. 지침서 완료 2603
2026-03-23 Kicad 기본파일 2603
2026-04-09 ms_board_V3 회로설계 1차 내용정리
2026-04-09 mcp 업데이트
2026-04-10 chore: gitignore 정리 - Down_Lib 추적 제거, 빌드/MCP 폴더 제외 추가
2026-04-11 kicad: update Multi_Mega_Main_V1, add SOT96P237X111-3N footprint, update MyLib_Active symbol
2026-04-14 회로도 구성 완료
2026-05-07 feat: 메가소닉 제어 및 빌드 설정 1차 수정
2026-05-07 chore: CubeMX 생성물 및 STM32 스캐폴딩 2차 반영
2026-05-07 docs: 매뉴얼 및 문서 산출물 3차 반영
2026-05-07 feat: Attiny85 dimmer main.cpp 수정
2026-05-07 chore: KiCad 아트웍 및 라이브러리 변경 반영
2026-05-07 chore: .history 폴더 무시 규칙 추가
